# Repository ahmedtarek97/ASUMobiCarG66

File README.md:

# ASUMobiCarG66
Smart Car Project
# Team Members
- Ahmed Abdel Salam Sayed
- Ahmed Sherif Mahmoud 
- Ahmed Talaat Abdel Gayed
- Ahmed Khaled Salah EL Din
- Ahmed Sayed Galal 
- Ahmed Sayed Ali 
- Ahmed Mahmoud Hamed Mahmoud EL Sherif
- Ahmed Ali Mohamed 
- Ahmed Tarek Hussin
- Ahmed Essam EL Din Mohamed Ahmed 
## Car Video 1 (Avoid obstacles)
https://www.youtube.com/watch?v=eO3J1CVVM0M
## Car Video 2 (Line tracking)
https://www.youtube.com/watch?v=YKVbSyOhMPY
## Car Video 3 (Certain angles)
https://www.youtube.com/watch?v=24bBdJ4Nc2E
## Car Video 4 (Certain distances)
https://www.youtube.com/watch?v=lTEOO76j08c
## Car Video 5 (Moving square , circle and infinity)
https://www.youtube.com/watch?v=4ortyBH39Ps

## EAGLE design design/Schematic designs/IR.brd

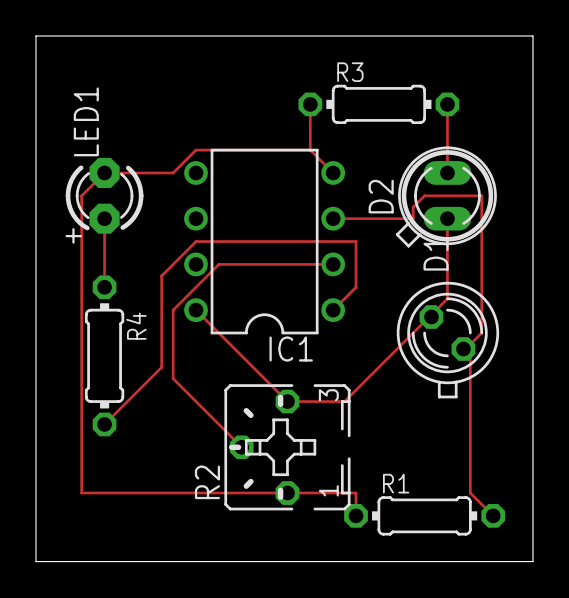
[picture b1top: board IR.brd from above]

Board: 2 copper layers, 27.6 x 29.2 mm, 8 parts (0 on the bottom side), 7 nets.

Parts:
D1: BPX65
D2: SFH482
IC1: LM358N; DIL08
LED1: LED3MM
R1, R3, R4: 0204/7
R2: B25P

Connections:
GND: IC1.4, LED1.K, R1.1, R2.A, R3.1
unnamed: D2.K, R3.2
unnamed: D1.A, IC1.3, R1.2
unnamed: IC1.2, R2.S
unnamed: IC1.1, R4.2
unnamed: LED1.A, R4.1
VCC: D1.K, D2.A, IC1.8, R2.E

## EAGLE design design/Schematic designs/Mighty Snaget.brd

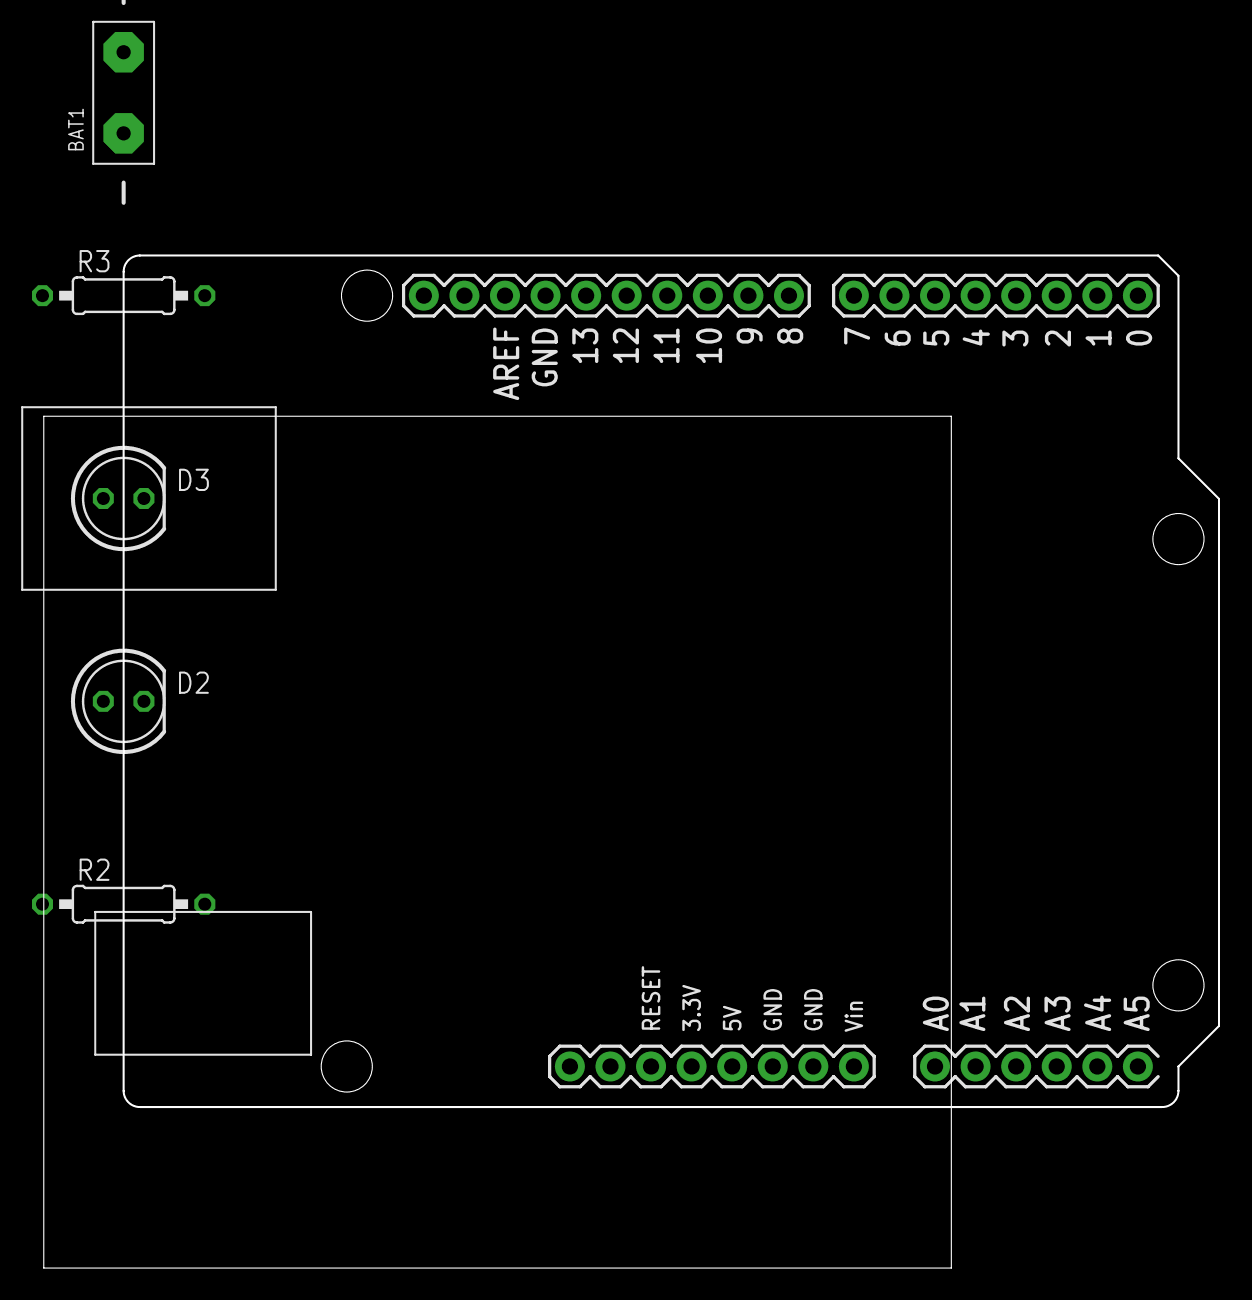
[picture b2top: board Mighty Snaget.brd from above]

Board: 2 copper layers, 73.6 x 63.4 mm, 6 parts (0 on the bottom side), 7 nets, no tracks yet.

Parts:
BAT1: DC-POWER
D2, D3: LED5MM
R2, R3: 200‎Ω; 0207/10
U3: ARDUINO_UNO

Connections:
unnamed: D2.A, R2.2
unnamed: D2.K, D3.K, U3.GND
unnamed: R2.1, U3.2
unnamed: D3.A, R3.2
unnamed: R3.1, U3.3
unnamed: BAT1.-, U3.GND.
unnamed: BAT1.+, U3.VIN

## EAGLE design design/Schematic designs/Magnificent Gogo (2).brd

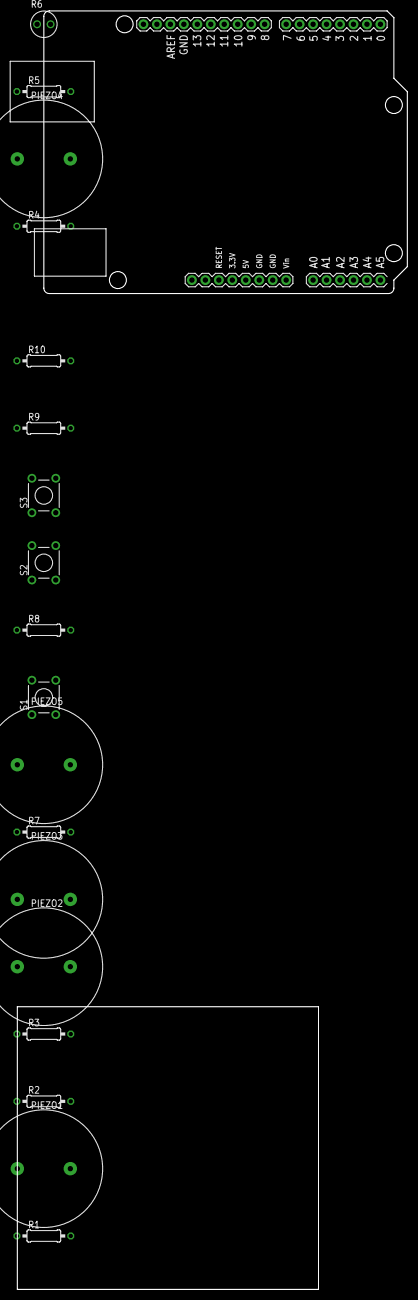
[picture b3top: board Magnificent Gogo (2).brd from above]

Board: 2 copper layers, 73.6 x 241.2 mm, 19 parts (0 on the bottom side), 9 nets, no tracks yet.

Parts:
PIEZO1, PIEZO2, PIEZO3, PIEZO4, PIEZO5: PIEZO-22MM
R1, R2, R3, R4, R7: 100‎Ω; 0207/10
R5: 4.7k‎Ω; 0207/10
R6: PHOTORESISTOR-2.54
R8, R9, R10: 10k‎Ω; 0207/10
S1, S2, S3: TL1105
U1: ARDUINO_UNO

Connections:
unnamed: PIEZO3.P$1, R3.2
unnamed: PIEZO2.P$1, R2.2
unnamed: PIEZO1.P$1, R1.2
unnamed: R4.2, U1.9
unnamed: PIEZO4.P$1, R4.1
unnamed: PIEZO4.P$2, U1.GND
unnamed: R5.2, U1.GND.
unnamed: R5.1, R6.P$1, U1.A0
unnamed: R6.P$2, U1.5V

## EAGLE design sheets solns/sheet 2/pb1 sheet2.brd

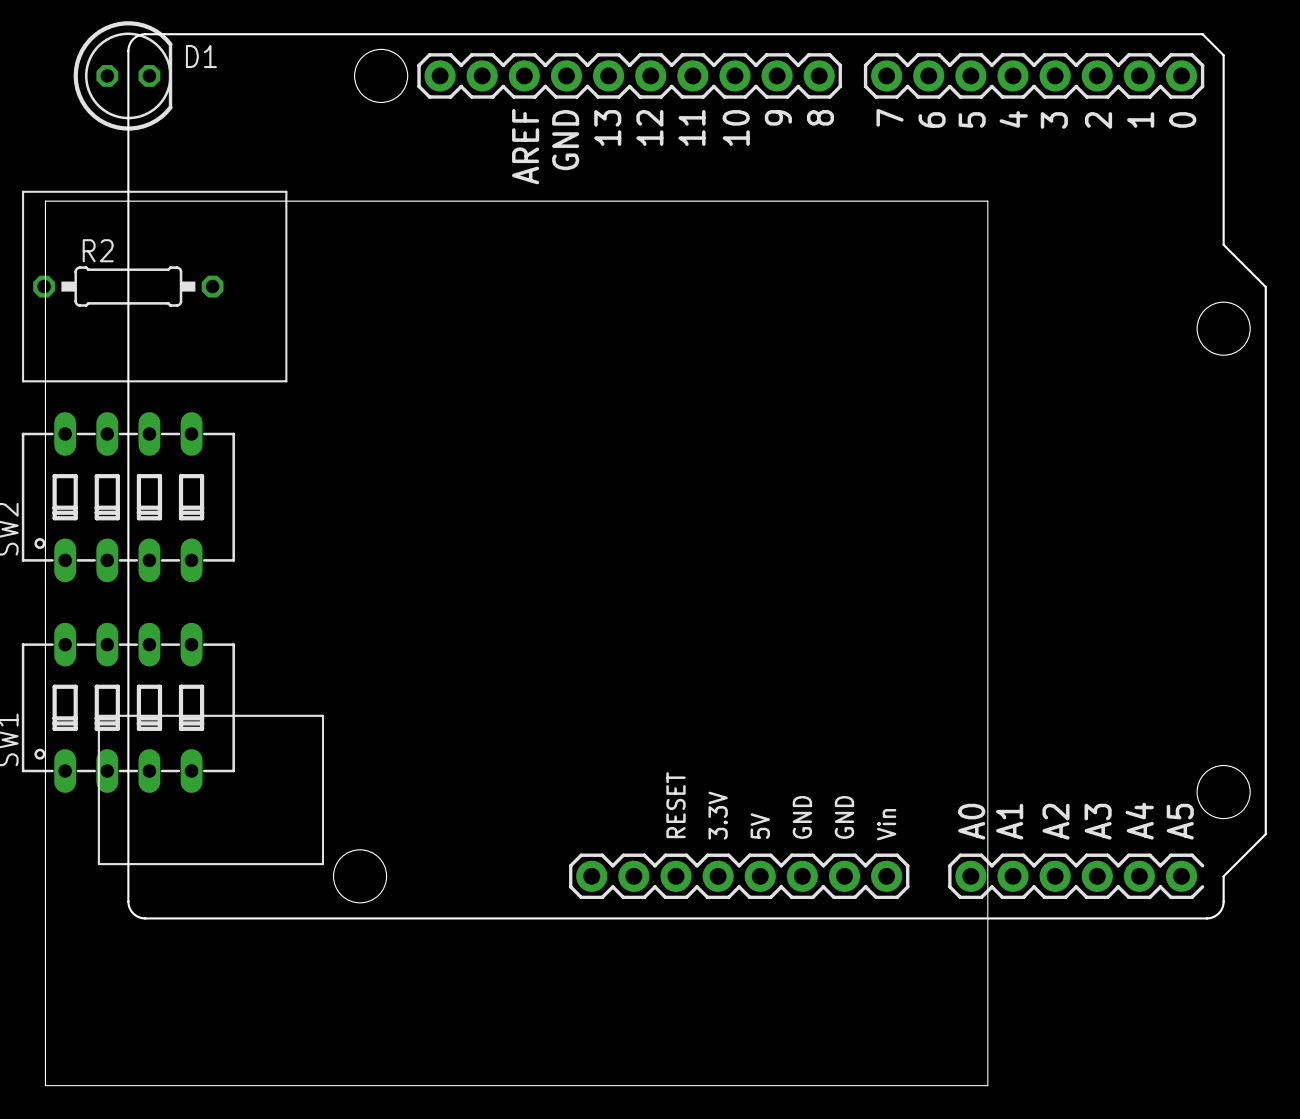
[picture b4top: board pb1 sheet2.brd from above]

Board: 2 copper layers, 73.6 x 63.4 mm, 5 parts (0 on the bottom side), 12 nets, no tracks yet.

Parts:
D1: LED5MM
R2: 220‎Ω; 0207/10
SW1, SW2: DIP04YL
U1: ARDUINO_UNO

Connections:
unnamed: SW1.1, SW1.2, SW1.3, SW1.4, SW2.1, SW2.2, SW2.3, SW2.4, U1.5V
unnamed: SW1.8, U1.0
unnamed: SW1.7, U1.1
unnamed: SW1.6, U1.2
unnamed: SW1.5, U1.3
unnamed: SW2.8, U1.4
unnamed: SW2.7, U1.5
unnamed: SW2.6, U1.6
unnamed: SW2.5, U1.7
unnamed: D1.A, R2.1
unnamed: D1.K, U1.GND.
unnamed: R2.2, U1.8

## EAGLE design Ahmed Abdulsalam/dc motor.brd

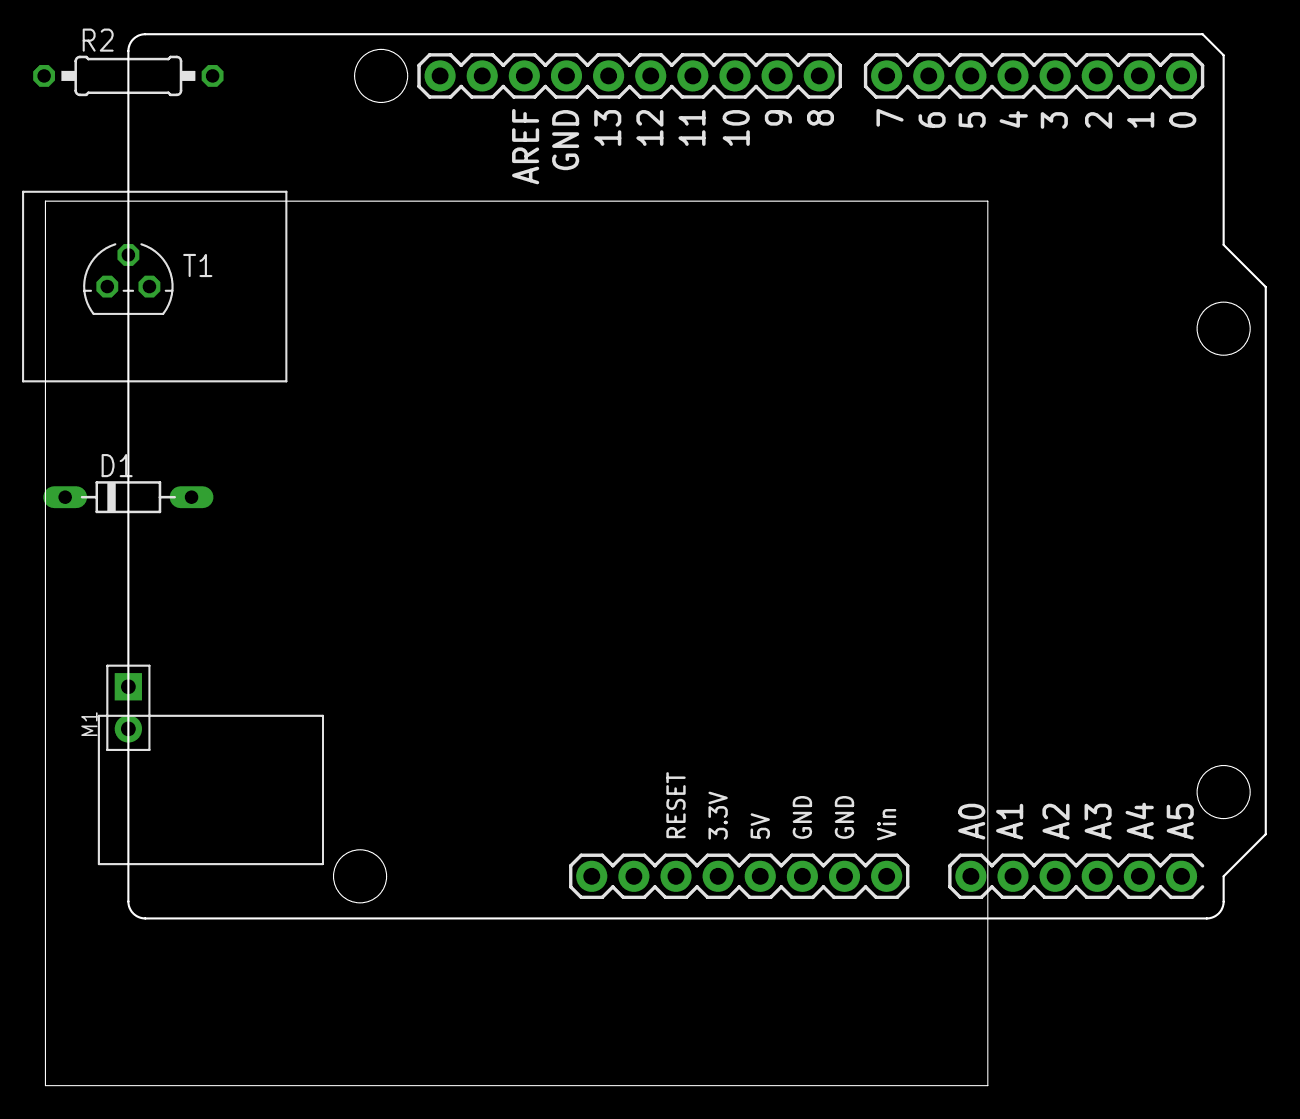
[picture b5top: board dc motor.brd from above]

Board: 2 copper layers, 73.6 x 63.4 mm, 5 parts (0 on the bottom side), 5 nets, no tracks yet.

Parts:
D1: D-7.5
M1: 2P-2.54-65/35MIL
R2: 1k‎Ω; 0207/10
T1: TO92
U1: ARDUINO_UNO

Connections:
unnamed: D1.C, M1.1, U1.5V
unnamed: D1.A, M1.2, T1.1
unnamed: R2.1, T1.2
unnamed: R2.2, U1.A0
unnamed: T1.3, U1.GND.

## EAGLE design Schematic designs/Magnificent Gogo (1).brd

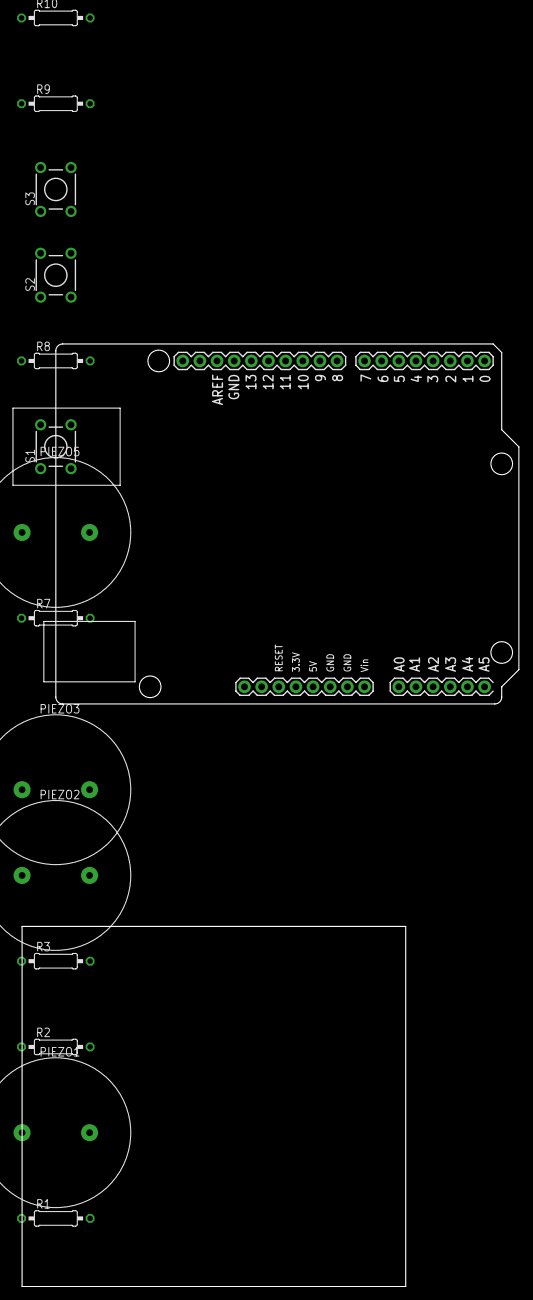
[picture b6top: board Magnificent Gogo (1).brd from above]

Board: 2 copper layers, 15 parts (0 on the bottom side), 13 nets, no tracks yet.

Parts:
PIEZO1, PIEZO2, PIEZO3, PIEZO5: PIEZO-22MM
R1, R2, R3, R7: 100‎Ω; 0207/10
R8, R9, R10: 10k‎Ω; 0207/10
S1, S2, S3: TL1105
U1: ARDUINO_UNO

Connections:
unnamed: PIEZO3.P$1, R3.2
unnamed: PIEZO2.P$1, R2.2
unnamed: PIEZO1.P$1, R1.2
unnamed: R7.2, R8.2, R9.2, R10.2, U1.GND..
unnamed: PIEZO5.P$2, U1.8
unnamed: PIEZO5.P$1, R7.1
unnamed: S1.2, S2.2, S3.2, U1.5V
unnamed: R8.1, S1.1
unnamed: S1.3, U1.A0
unnamed: R9.1, S2.1
unnamed: S2.3, U1.A1
unnamed: R10.1, S3.1
unnamed: S3.3, U1.A2

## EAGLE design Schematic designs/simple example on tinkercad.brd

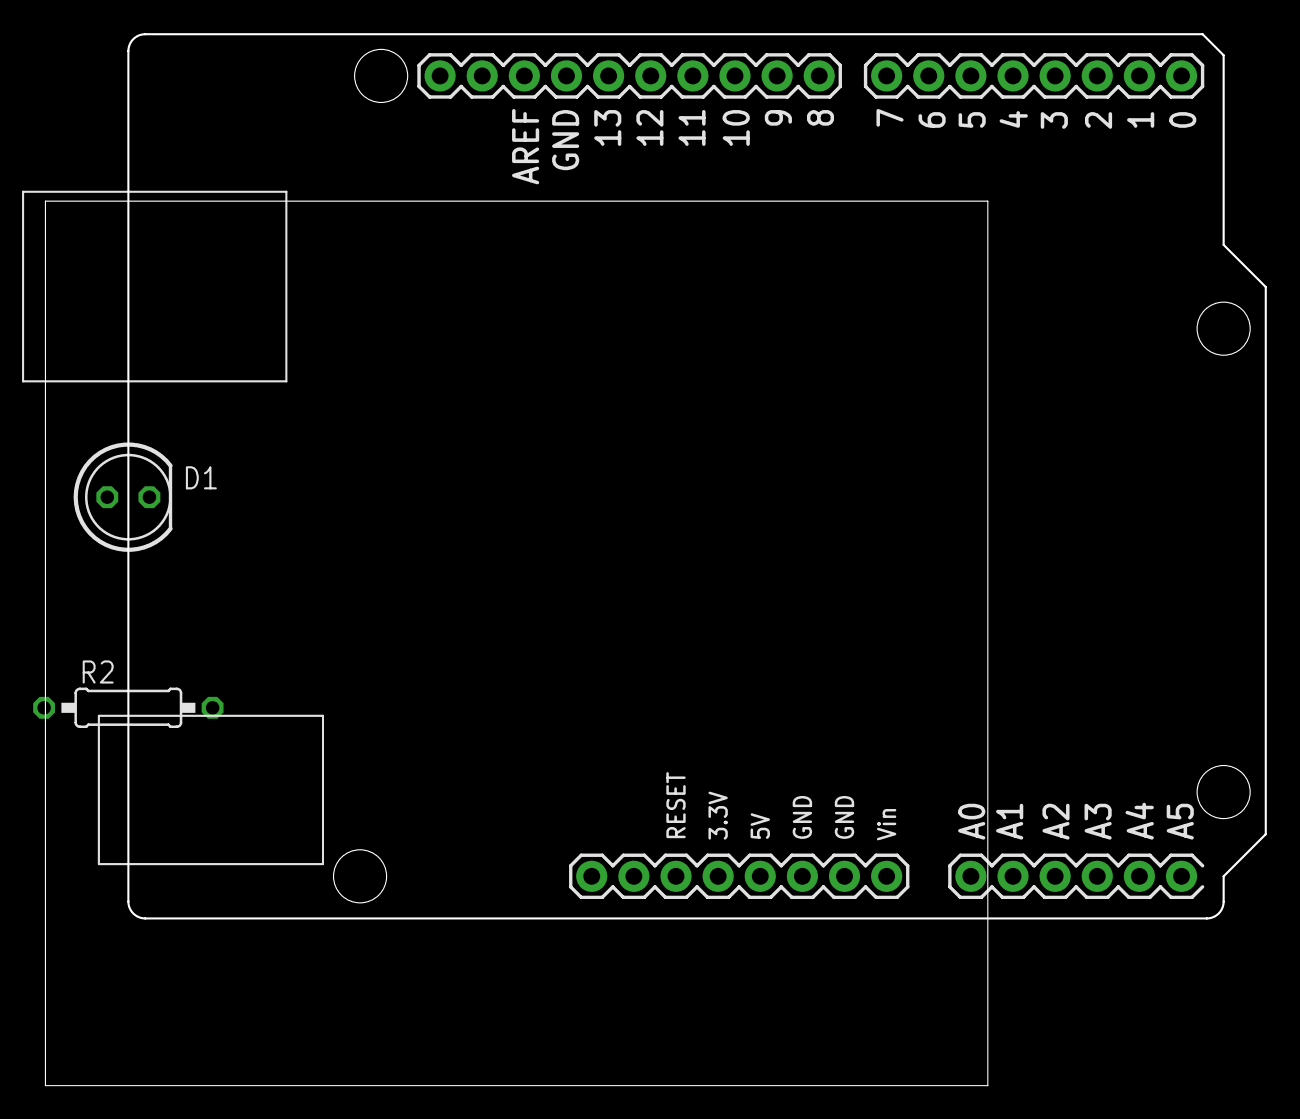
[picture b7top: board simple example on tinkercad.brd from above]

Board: 2 copper layers, 73.6 x 63.4 mm, 3 parts (0 on the bottom side), 3 nets, no tracks yet.

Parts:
D1: LED5MM
R2: 220‎Ω; 0207/10
U1: ARDUINO_UNO

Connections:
unnamed: D1.K, U1.GND..
unnamed: R2.2, U1.13
unnamed: D1.A, R2.1

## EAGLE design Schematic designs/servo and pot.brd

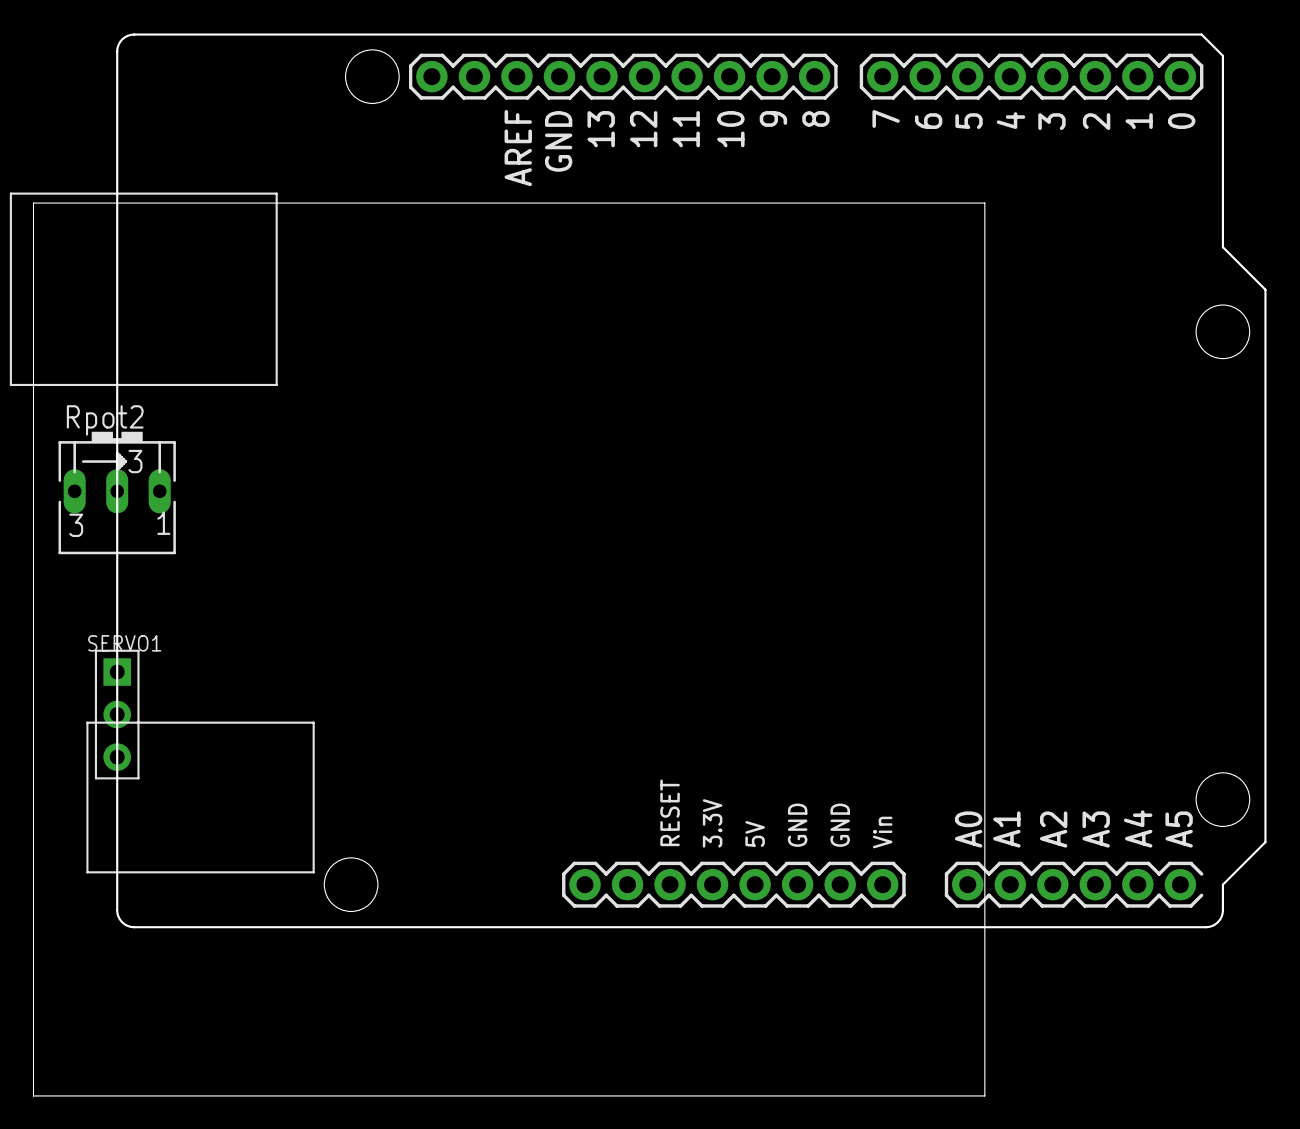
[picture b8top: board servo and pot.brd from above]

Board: 2 copper layers, 73.6 x 63.4 mm, 3 parts (0 on the bottom side), 5 nets, no tracks yet.

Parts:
Rpot2: 250k‎Ω; B25V
SERVO1: 1X3P-2.54-2.54-11.6-3.0-BLACK-MALE
U1: ARDUINO_UNO

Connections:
unnamed: SERVO1.1, U1.GND.
unnamed: Rpot2.A, SERVO1.2, U1.5V
unnamed: SERVO1.3, U1.7
unnamed: Rpot2.E, U1.GND..
unnamed: Rpot2.S, U1.A0

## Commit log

2018-02-22 git upload commands
2018-02-22 Add files via upload
    AVR Guide
2018-02-22 Flashing LED
2018-02-22 LED Control
    Controlling LED using button
2018-02-22 LED flashing
2018-02-22 LEDS FLASHING
2018-02-22 1st & 2nd Question solutions
2018-02-22 generate square wave
2018-02-22 bouncing
2018-02-27 using two switches to control led behavior
2018-02-28 initial Code
2018-02-28 Android Control App
2018-03-03 Ultrasonic and LCD
2018-03-03 LCD and group names
2018-03-03 LCD and group names moving
2018-03-03 Adding Bluetooth Sensor
2018-03-11 Editing the Code
    Code Beta 1
2018-03-26 Create AVR EXAMPLES
2018-03-26 AVR EX1 counter of clicks
2018-03-26 sheet2/problem1/
2018-03-26 Create problem 1
2018-03-27 Create problem 2
2018-03-27 Create problem 3 (avr)
2018-03-28 pb1 sheet 2
2018-03-28 IR sensor
    the design of IR sensors
2018-03-29 Create problem 4
2018-03-29 Create problem 5
2018-03-29 app ( trial)
2018-03-29 Create problem 6
2018-03-29 Avr example
    sheet 1 problem 2
2018-03-29 sheet 1 p1
2018-03-29 sheet 1 p 2
2018-03-29 sheet 2 p1
2018-03-30 Create General problems
2018-03-30 Create Slides Problems
2018-03-30 Create ex1
2018-03-30 Create ex2
2018-03-30 line follower code using IR
2018-03-31 measuring temp using thermistor
2018-03-31 measuring temp using thermistor
    the output is written in celsius and fahrenheit
2018-03-31 Thermistor & LCD
2018-03-31 Create Ahmed Ali
2018-03-31 Update Ahmed Ali
2018-03-31 Update and rename Ahmed Ali to Q3
2018-03-31 Add files via upload
    https://www.tinkercad.com/things/7XvlpEPy14j-start-simulating/editel?collectionid=OIYJ88OJ3OPN3EA&lessonid=EHD2303J3YPUS5Z&magic=ba9e61a52958912d77aa472d96ec6ae5756e1a89&projectid=OIYJ88OJ3OPN3EA&t=1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
2018-03-31 Using DHT11 to measure humidity
2018-03-31 DHT11 and LCD
2018-03-31 Update Q3
2018-03-31 Add files via upload
    https://www.tinkercad.com/things/cjTkbtg43H7-surprising-uusam-blad/editel?tenant=circuits?sharecode=PPMJLeJsnTvmZFfcyJwLyffgmmg3ebdSSMPEbqbHry8=
2018-03-31 Create intrupt
2018-03-31 pb2 sheet2
2018-03-31 sheet2 pb
2018-03-31 Create inturrupt exAmple 2
2018-03-31 learning case 1
2018-03-31 learning case 2
2018-03-31 learning case 3
2018-04-01 Without Calibratio
2018-04-01 Before Calibration
2018-04-01 After Calibrating
2018-04-01 Rename RC_car_final.ino to RC Smart Car Final Codes/RC_car_final.ino
2018-04-01 Final Phase 1 Code
2018-04-01 Rename RC_car_final.ino to RC_car_Movement.ino
2018-04-02 Update Slides Problems
2018-04-02 Create excepected avr code
2018-04-02 multiple tone buzzer
2018-04-02 sheet 2 solns
2018-04-02 line follower codec2 arduino
2018-04-02 DC motor example/
2018-04-02 ASUMobiCarG66/DC motor/
2018-04-03 Create line_follower(test)
2018-04-03 Update General problems
2018-04-04 Update line_follower(test)
2018-04-04 Create Q3 SHEET 2
2018-04-04 Q3 SHEET 2
2018-04-04 Update Testing
2018-04-04 Create sheet2 q3(another solution)
2018-04-05 Create analog input digital output for 1 led
2018-04-05 Create sheet2 q4G
2018-04-05 Create ultrasonic
2018-04-06 application with line tracking option
2018-04-06 power calcs of the project model
2018-04-06 tone pitch follower
2018-04-07 Create String constructors
2018-04-07 Create PinG
2018-04-07 Create edge detection
2018-04-07 pitch follower buzzer
2018-04-08 Create lcd
2018-04-08 Create lcd2
2018-04-08 Create lcd 3
2018-04-09 Create avr timer
2018-04-09 Create timers
2018-04-10 PIR sensor code
2018-04-10 ultrasonic sensor code
2018-04-10 temperature sensor code
2018-04-10 Create first trial for IR sensor
2018-04-10 a book for arduino similar projects
2018-04-12 Create comprator
2018-04-12 Rename comprator to comprator.c
2018-04-17 Create how to set bits
2018-04-21 Add files via upload
    Q1 Sheet2
2018-04-21 Add files via upload
    Q2 Sheet 2
2018-04-21 Add files via upload
    Q3 Sheet2
2018-04-21 Add files via upload
    Q4 Sheet 2
2018-04-21 schematic design ASUMOBicar
2018-04-21 Rename CAR schematic design.sch to Schematic designs/CAR schematic design.sch
2018-04-21 phase 1 schematic design
2018-06-24 Create Main theme
2018-06-24 Create Main
2018-07-01 Create draw
2018-07-04 Rename 21.ino to Trials/21.ino
2018-07-04 Rename Q3 #SHEET 2 to sheet2/Q3 #SHEET 2
2018-07-04 Rename Q3 SHEET 2 to sheet2/Q3_SHEET2.ino
2018-07-04 Rename Q2 sheet 2.atsln to sheet2/Q2 sheet 2.c
2018-07-04 Rename Q3 sheet 2.atsln to sheet2/Q3 sheet 2.atsln
2018-07-04 Rename Q4 Sh2.atsln to sheet2/Q4 Sh2.atsln
2018-07-04 Rename pb1 sheet2.brd to sheet2/pb1 sheet2.brd
2018-07-04 Rename sh2_PB5.ino to sheet2/sh2_PB5.ino
2018-07-04 Rename q1 Sh2.atsln to sheet2/q1 Sh2.atsln
2018-07-04 Rename pb1 sheet2.ino to sheet2/pb1 sheet2.ino
2018-07-04 Rename sh2_pb2.ino to sheet2/sh2_pb2.ino
2018-07-04 Rename sheet_2_pb_3.ino to sheet2/pb_3.ino
2018-07-04 Rename sheet2_pb6.ino to sheet2/pb6.ino
2018-07-04 Rename sheet2_pb5.ino to sheet2/pb5.ino
2018-07-04 Rename sheet2_pb4.ino to sheet2/pb4.ino
2018-07-04 Rename sheet2_pb3.ino to sheet2/pb3.ino
2018-07-04 Rename sheet2_pb2.ino to sheet2/pb2.ino
2018-07-04 Rename sheet2_pb1.ino to sheet2/pb1.ino
2018-07-04 Rename sheet 2 pb 1.ino to sheet2/pb 1.ino
2018-07-04 Rename sheet2_p2.ino to sheet2/p2.ino
2018-07-04 Rename p2.ino to p2Galal.ino
2018-07-04 Rename sheet2.ino to sheet2/LiquidCrystal.ino
2018-07-04 Rename sheet2 q4G to sheet2/q4G.ino
2018-07-04 Rename sheet2 q3(another solution) to sheet2/q3(another solution).ino
2018-07-04 Rename sh2_pb6.ino to sheet2/sh2_pb6.ino
2018-07-04 Rename sh2_pb4.ino to sheet2/sh2_pb4.ino
2018-07-04 Rename sh2_pb3.ino to sheet2/sh2_pb3.ino
2018-07-04 Rename temperature sensor to temperature sensor.ino
2018-07-04 Rename q2.ino to Sheet 1 Solutions/q2.ino
2018-07-04 Rename q3.ino to Sheet 1 Solutions/q3.ino
2018-07-04 Rename sheet1pb2.ino to Sheet 1 Solutions/sheet1pb2.ino
2018-07-04 Rename sheet1pb1.ino to Sheet 1 Solutions/sheet1pb1.ino
2018-07-04 Rename line_follower(test) to Trials/line_follower(test).ino
2018-07-04 Rename Blink.ino to Sheet 1 Solutions/Blink.ino
2018-07-04 Rename Q2 Sheet4.atsln to Sheet 4/Q2 Sheet4.atsln
2018-07-04 Rename Blinking_one_led.ino to Sheet 1 Solutions/Blinking_one_led.ino
2018-07-04 Rename AVR.atsln to Sheet 1 Solutions/AVR.atsln
2018-07-04 Rename Example_4_Variable_Resistor_sensor.ino to sensors examples/Example_4_Variable_Resistor_sensor.ino
2018-07-04 Rename Example_5_Light_Sensor_led.ino to sensors examples/Example_5_Light_Sensor_led.ino
2018-07-04 Rename Example_7_Temprature_Sensor.ino to sensors examples/Example_7_Temprature_Sensor.ino
2018-07-04 Rename Q3 Sheet4.atsln to Sheet 4/Q3 Sheet4.atsln
2018-07-04 Rename IR.brd to Schematic designs/IR.brd
2018-07-04 Rename IR.sch to Schematic designs/IR.sch
2018-07-04 Rename PIR_sensor.ino to sensors examples/PIR_sensor.ino
2018-07-04 Rename LCD_group_name.ino to Good Arduino Examples/LCD_group_name.ino
2018-07-04 Rename LCD_group_names_moving.ino to Good Arduino Examples/LCD_group_names_moving.ino
2018-07-04 Rename dc motor.ino to Good Arduino Examples/dc motor.ino
2018-07-04 Rename line_follower.ino to Good Arduino Examples/line_follower.ino
2018-07-04 Rename edge detection to Good Arduino Examples/edge detection.ino
2018-07-04 Rename humidity_sensor_DHT11_.ino to sensors examples/humidity_sensor_DHT11_.ino
2018-07-04 Rename edge detection.ino to edge_detection.ino
2018-07-04 Rename LINEFOLLOWER.ino to Good Arduino Examples/LINEFOLLOWER.ino
2018-07-04 Rename intrrupt.ino to Good Arduino Examples/intrrupt.ino
2018-07-04 Rename tempSensor.ino to sensors examples/tempSensor.ino
2018-07-04 Rename temp_sensor_and_LCD.ino to sensors examples/temp_sensor_and_LCD.ino
2018-07-04 Rename temperature sensor.ino to sensors examples/temperature sensor.ino
2018-07-04 Rename thermistor.ino to sensors examples/thermistor.ino
2018-07-04 Rename ultaeasonic sensor to sensors examples/ultaeasonic sensor
2018-07-04 Rename ultrasonic_and_LCD.ino to sensors examples/ultrasonic_and_LCD.ino
2018-07-04 Rename DHT_and_LCD.ino to Good Arduino Examples/DHT_and_LCD.ino
2018-07-04 Rename sketch_apr03a.ino to Ahmed Talaat/sketch_apr03a.ino
2018-07-04 Rename sketch_apr06a.ino to Ahmed Talaat/sketch_apr06a.ino
2018-07-04 Rename sketch_apr07a.ino to Ahmed Talaat/sketch_apr07a.ino
2018-07-04 Rename sketch_mar28a.ino to Ahmed Talaat/sketch_mar28a.ino
2018-07-04 Rename sketch_mar30a.ino to Ahmed Talaat/sketch_mar30a.ino
2018-07-04 Rename sketch_mar30b.ino to Ahmed Talaat/sketch_mar30b.ino
2018-07-04 Rename PinG to Good Arduino Examples/PinG.ino
2018-07-04 Rename TMP36.brd to Schematic designs/TMP36.brd
2018-07-04 Rename Mighty Snaget.brd to Schematic designs/Mighty Snaget.brd
2018-07-04 Rename Testing to Good Arduino Examples/Testing.ino
2018-07-04 Rename String constructors to Good Arduino Examples/String constructors.ino
2018-07-04 Rename pitch_follower.ino to Good Arduino Examples/pitch_follower.ino
2018-07-04 Rename servo and pot.brd to Schematic designs/servo and pot.brd
2018-07-04 Rename Swanky Duup-Tumelo1.ino to Good Arduino Examples/Swanky Duup-Tumelo1.ino
2018-07-04 Rename Incredible Jarv-Turing1.ino to Good Arduino Examples/Incredible Jarv-Turing1.ino
2018-07-04 Rename simple example on tinkercad.brd to Schematic designs/simple example on tinkercad.brd
2018-07-04 Rename simple example on tinkercad.ino to Ahmed Abdulsalam/simple example on tinkercad.ino
2018-07-04 Rename Schematic designs/simple example on tinkercad.brd to Ahmed Abdulsalam/Schematic designssimple example on tinkercad.brd
2018-07-04 Rename Schematic designssimple example on tinkercad.brd to simple example on tinkercad.brd
2018-07-04 Rename Magnificent Gogo (1).brd to Schematic designs/Magnificent Gogo (1).brd
2018-07-04 Rename Magnificent Gogo (2).brd to Schematic designs/Magnificent Gogo (2).brd
2018-07-04 Rename Mighty Snaget1.ino to Good Arduino Examples/Mighty Snaget1.ino
2018-07-04 Rename codeblouetooth.c to EL Sherif/codeblouetooth.c
2018-07-04 Rename dc motor.brd to Ahmed Abdulsalam/dc motor.brd
2018-07-04 Rename servo and pot.ino to Good Arduino Examples/servo and pot.ino
2018-07-04 Rename TMP36.ino to Ahmed Abdulsalam/TMP36.ino
2018-07-05 Create ultrasonic distance function
2018-07-05 Rename excepected avr code to EL Sherif/excepected avr code.c
2018-07-05 Rename blink led.atsln to AVR/TIMER EXAMPLE/blink led.atsln
2018-07-05 Rename analog input digital output for 1 led to Good Arduino Examples/analog input digital output for 1 led.ino
2018-07-05 Update ultrasonic distance function
2018-07-06 Create final_application
2018-07-06 Create app
2018-07-06 Add files via upload
    The final version of the application
2018-07-06 Add files via upload
    application with line tracking option
2018-07-06 The final version of the mobile application
2018-10-22 simplify files
2018-10-22 better view
2018-10-22 final view
